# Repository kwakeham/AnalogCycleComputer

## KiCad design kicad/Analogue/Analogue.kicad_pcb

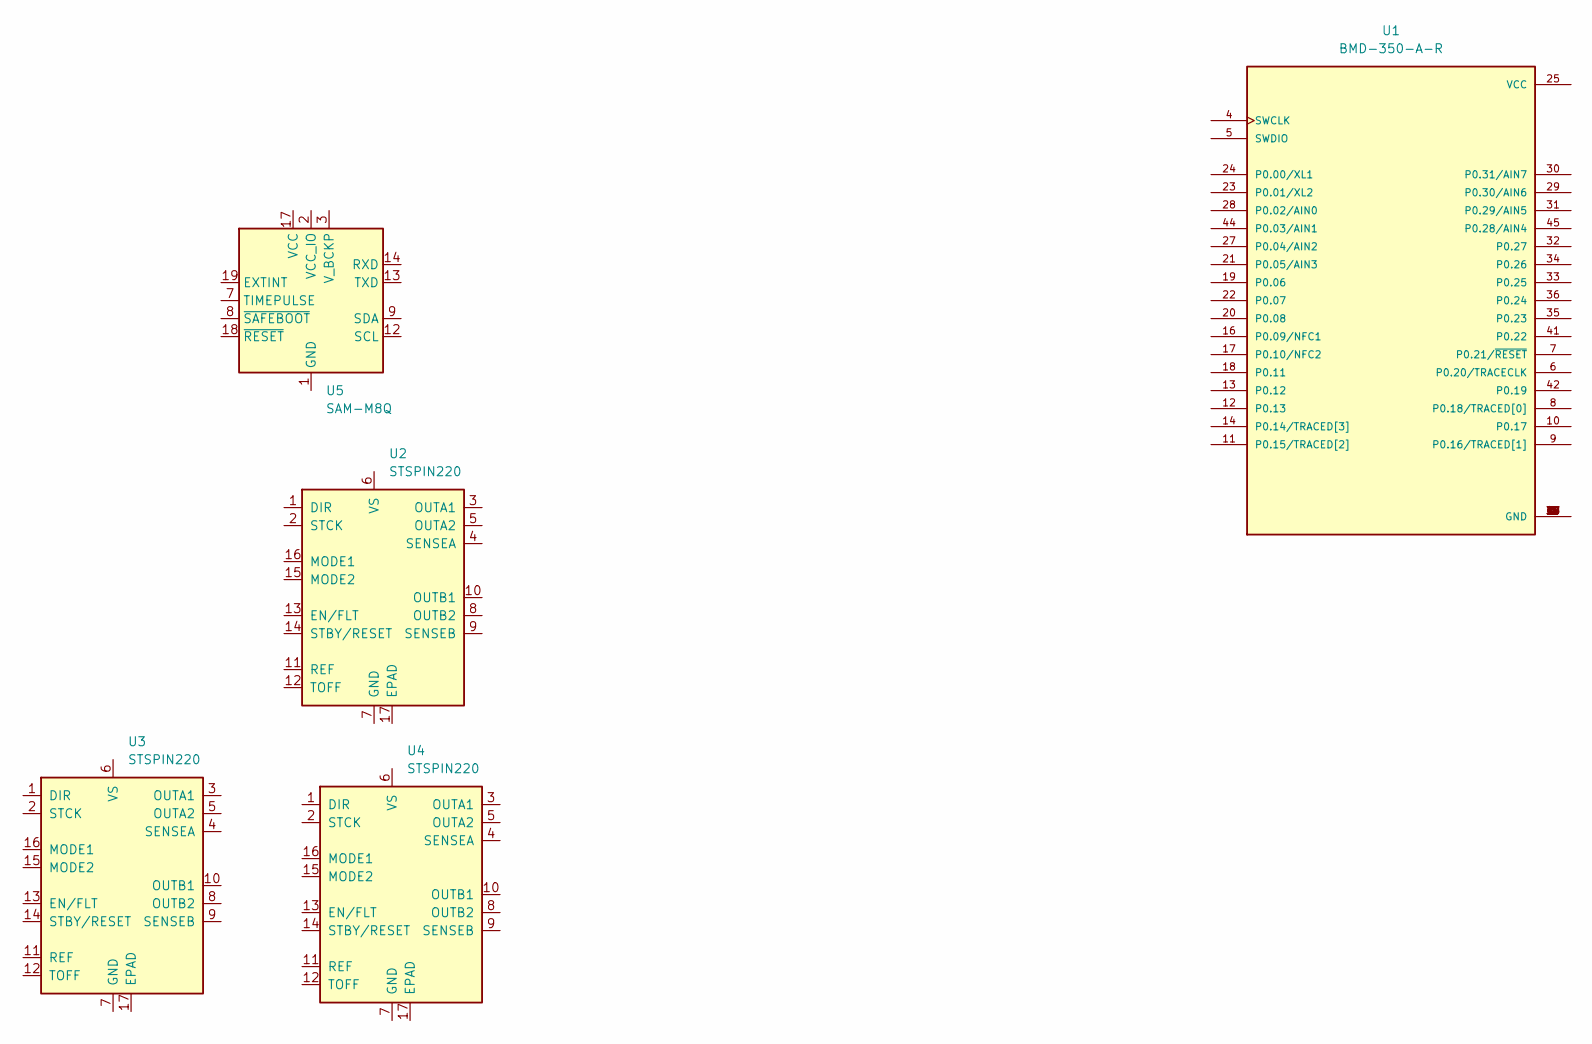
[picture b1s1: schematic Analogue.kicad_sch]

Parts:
U1: BMD-350-A-R; XCVR_BMD-350-A-R; PARTREV 2.0
U2, U3, U4: STSPIN220; VQFN-16-1EP_3x3mm_P0.5mm_EP1.8x1.8mm
U5: SAM-M8Q; ublox_SAM-M8Q

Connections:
unnamed: U1.1 (GND), U1.2 (GND), U1.3 (GND), U1.15 (GND), U1.26 (GND), U1.37 (GND), U1.38 (GND), U1.39 (GND), U1.40 (GND), U1.43 (GND), U1.46 (GND), U1.47 (GND)
unnamed: U5.1 (GND), U5.4 (GND), U5.5 (GND), U5.6 (GND), U5.10 (GND), U5.11 (GND), U5.15 (GND), U5.16 (GND), U5.20 (GND)

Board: 2 copper layers, 5 parts (0 on the bottom side), 2 nets, no tracks yet.

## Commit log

2022-01-26 Adding libraries
